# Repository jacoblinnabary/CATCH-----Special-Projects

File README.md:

# CATCH-----Special-Projects
Carolina Adapts Toys for Children projects aimed towards building engineering skills while providing accesibility to our community

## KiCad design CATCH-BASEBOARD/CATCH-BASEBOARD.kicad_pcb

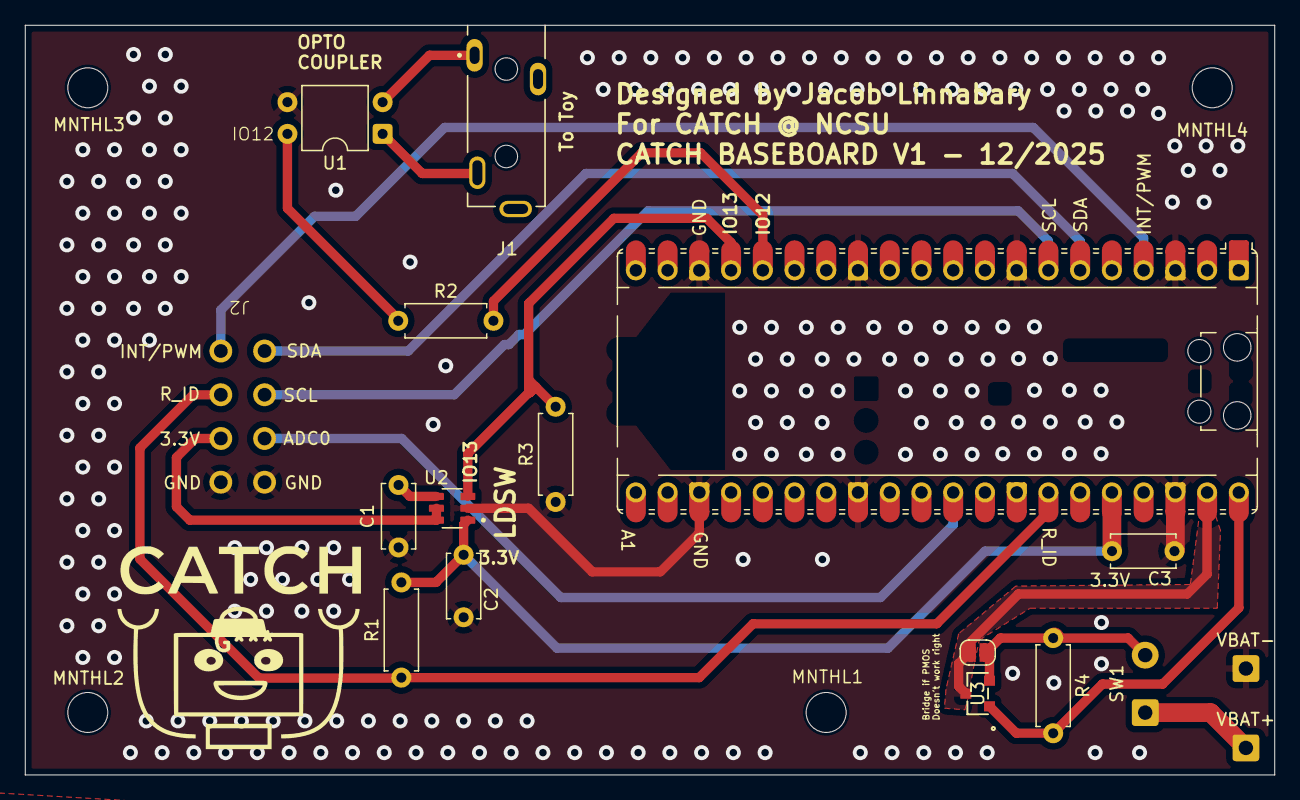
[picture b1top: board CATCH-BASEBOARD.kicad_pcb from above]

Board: 2 copper layers, 100.0 x 60.0 mm, 21 parts (0 on the bottom side), 18 nets.

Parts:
A1: RaspberryPi_Pico; RaspberryPi_Pico_Common_Unspecified
C1: 220p; C_Disc_D5.0mm_W2.5mm_P5.00mm
C2, C3: 1u; C_Disc_D5.0mm_W2.5mm_P5.00mm
J1: SJ3-35083B-TR; SAMESKY_SJ3-35083B-TR
J2: Conn_02x04_Odd_Even; POGO_2x4_THT
JP1: SolderJumper_2_Open; SolderJumper-2_P1.3mm_Open_RoundedPad1.0x1.5mm
MNTHL1, MNTHL2, MNTHL3, MNTHL4: MountingHole_3.2mm_M3
R1, R2: 10k; R_Axial_DIN0207_L6.3mm_D2.5mm_P7.62mm_Horizontal
R3, R4: 100k; R_Axial_DIN0207_L6.3mm_D2.5mm_P7.62mm_Horizontal
SW1: SW_SPST; SolderWire-0.5sqmm_1x02_P4.6mm_D0.9mm_OD2.1mm
U1: PC817; DIP-4_W7.62mm
U2: TPS22918DBVR; SOT95P280X145-6N
U3: DMG2305UX-13; DMG2305UX
VBAT+: VBAT+; SolderWire-0.5sqmm_1x01_D0.9mm_OD2.1mm
VBAT-: VBAT -; SolderWire-0.5sqmm_1x01_D0.9mm_OD2.1mm

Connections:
+3V3: A1.36 (3V3), C2.1, C3.1, R1.2, U2.1 (VIN)
ADC0: A1.31 (GPIO26_ADC0), J2.3
GND: A1.3 (GND), A1.8 (GND), A1.13 (GND), A1.18 (GND), A1.23 (GND), A1.28 (GND), A1.38 (GND), C1.1, C2.2, C3.2, J2.1, J2.2, R3.1, U1.3, U2.2 (GND), VBAT-.1
GPIO12: A1.16 (GPIO12), R2.2
GPIO13: A1.17 (GPIO13), R3.2, U2.3 (ON)
INTERRUPT/PWM1: A1.4 (GPIO2), J2.8
JACK MIDDLE: J1.1, U1.2
JACK_LEFT: J1.2, U1.1
unnamed: JP1.2 (B), R4.1, SW1.2 (B), U3.2 (S)
unnamed: R2.1, U1.4
unnamed: SW1.1 (A), VBAT+.1
unnamed: C1.2, U2.4 (CT)
OUTPUT3.3: J2.4, U2.5 (QOD), U2.6 (VOUT)
R_ID_PIN: A1.34 (GPIO28_ADC2), J2.6, R1.1
SCL: A1.7 (GPIO5), J2.5
SDA: A1.6 (GPIO4), J2.7
VSYS: A1.39 (VSYS), JP1.1 (A), U3.3 (D)
VUSB: A1.40 (VBUS), R4.2, U3.1 (G)

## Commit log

2025-12-19 Add initial CATCH-BASEBOARD KiCad project files
    Added baseboard project files including schematic (.kicad_sch), PCB layout (.kicad_pcb), project settings (.kicad_pro, .kicad_prl), EDA models for SJ3_35083B_TR, and backup archives. This establishes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
    Schematic now contains all components going to be used, some pins have defined.
2025-12-20 ADDITIONS TO SCHEMATIC
    Fleshed out schematic more, added load switch and connectors. Imported new models. Need to work on battery logistics then start PCB.
2025-12-21 Fleshed Out Battery System
    Added safeties to the battery system, reducing potential harm when programming. Added parts, and updated schematic.
2025-12-22 Start of Layout
    Added final parts in the schematic (battery connections, switches), assigned footprints, and started layout. Added rough size of PCB, placed some components.
2025-12-23 Some Edits to layout
2025-12-24 First Layout Revision
2025-12-25 Fixed Schematic + Finished Layout v.1
    Layout still needs some touching up on, especially vias. I'll be changing it to fix all the errors on the DRC.
2025-12-26 Finished PCB
    Fixed some layout, added on board documentation.
